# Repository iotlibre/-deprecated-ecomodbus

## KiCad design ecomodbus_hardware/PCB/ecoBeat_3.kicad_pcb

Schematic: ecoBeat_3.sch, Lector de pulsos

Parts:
C1: 10nF; C_1206_HandSoldering
C2: 10uF; C_1206_HandSoldering
D1, D3: LED; LED-3MM
F1: Fuse; Fuse_Horizontal_RM10mm
J1: AC_input; bornier2
J2: Conn_MODBUS; bornier3
J3: Test_5V; SolderWirePad_single_0-8mmDrill
P1: CONN_VCC; Pin_Header_Straight_1x08
P2: CONN_DATOS; Pin_Header_Straight_1x08
R1, R2, R3, R4: 10K; R_1206
R5, R9: 20K; R_1206
R6, R8: 220; R_1206
R10: 120; R_1206
U1: WeMos_mini; D1_mini_board
U2: ACDC-5V; vigortronix
U3: MAX_485; SOIC-8-N

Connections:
/5.0V: C1.1, C2.1, J3.1, P1.8, R1.2, R2.2, R3.2, R4.2, R5.2, R8.2, U2.4 (5V+), U3.8 (VCC)
/L1: P1.5, R6.2
/driver: P2.5, R3.1, U3.3 (DE)
/receiver: P2.4, R2.1, U3.2 (~RE~)
/rx_wemos: P1.2, R1.1, U3.1 (RO)
/tx_wemos: P1.1, R4.1, U3.4 (DI)
GND: C1.2, C2.2, D1.1, D3.1, J2.3, P1.7, R9.1, U2.3 (5v-), U3.5 (GND)
unnamed: D1.2, R6.1
unnamed: D3.2, R8.1
unnamed: F1.1, J1.2
unnamed: F1.2, U2.1 (AC)
unnamed: J1.1, U2.2 (AC)
unnamed: J2.1, R5.1, R10.1, U3.6 (A)
unnamed: J2.2, R9.2, R10.2, U3.7 (B)

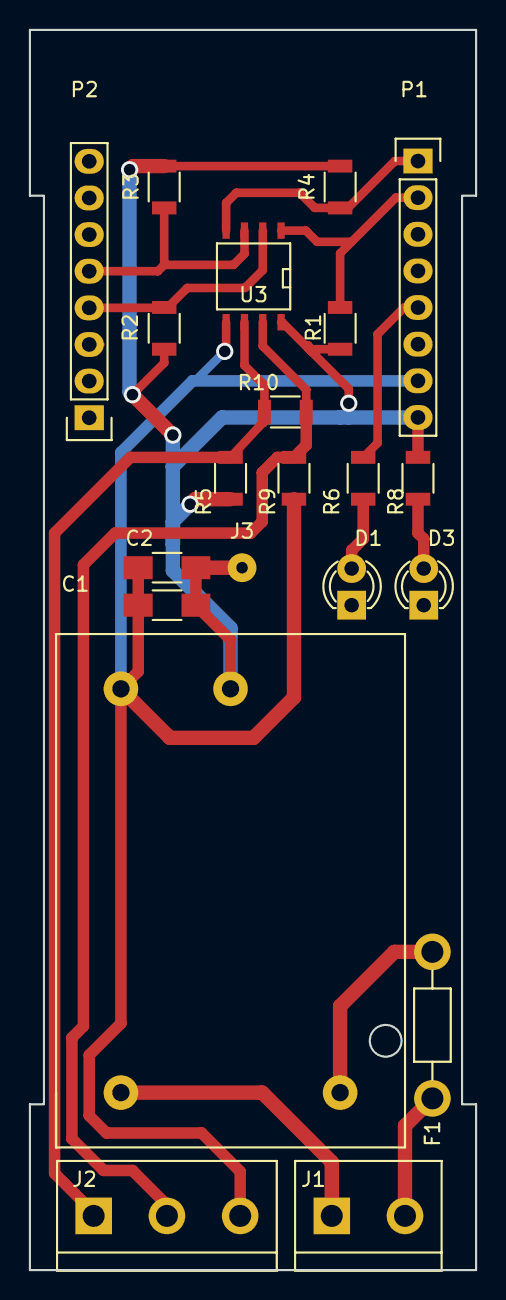
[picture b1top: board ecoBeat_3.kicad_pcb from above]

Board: 2 copper layers, 30.9 x 86.0 mm, 21 parts (0 on the bottom side), 14 nets.

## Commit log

2018-03-28 inicio_harddware
2018-03-28 menos
2018-04-02 hardware intermiedio
2018-04-03 primera version PCB para pruebas
2018-04-16 pdb 2
2018-07-10 primera version para probar
2018-07-16 version de fabricacion
2018-07-17 modificado pad fusible
2018-08-27 borrado ecobeat
